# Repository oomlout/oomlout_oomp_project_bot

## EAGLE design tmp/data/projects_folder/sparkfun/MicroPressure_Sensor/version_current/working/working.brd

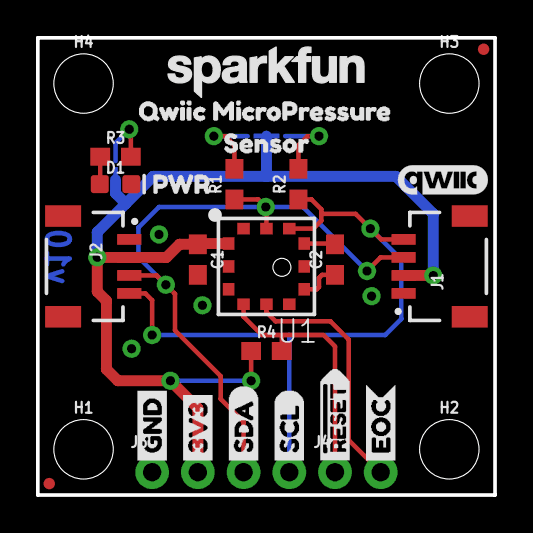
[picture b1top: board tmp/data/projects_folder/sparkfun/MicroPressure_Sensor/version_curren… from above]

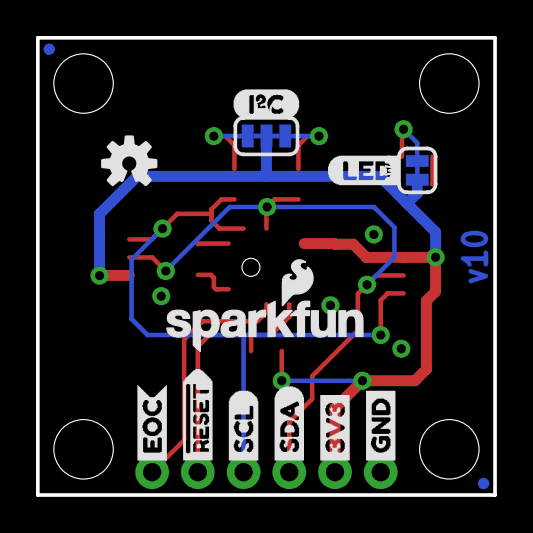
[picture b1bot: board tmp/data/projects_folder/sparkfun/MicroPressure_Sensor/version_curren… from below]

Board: 2 copper layers, 25.4 x 25.4 mm, 44 parts (14 on the bottom side), 12 nets.

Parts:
C1: 0.1uF; 0603
C2: 1nF; 0603
D1: RED; LED-0603
FD1, FD2, FD3, FD4: FIDUCIALUFIDUCIAL; FIDUCIAL-MICRO
FRAME1: FRAME-LETTER; CREATIVE_COMMONS
H1, H2, H3, H4: STAND-OFF
I2C: SMT-JUMPER_3_2-NC_TRACE_SILK
J1, J2: Qwiic; JST04_1MM_RA
J3: 1X04_NO_SILK
J4: 1X02_NO_SILK
LOGO1: QWIIC_LOGO_5MM; QWIIC_5MM
LOGO2: OSHW-LOGOS; OSHW-LOGO-S
LOGO3: SFE_LOGO_NAME_FLAME.1_INCH; SFE_LOGO_NAME_FLAME_.1
PWR: SMT-JUMPER_2_NC_TRACE_SILK
R1, R2, R4: 2.2k; 0603
R3: 1k; 0603
U1: MPR Series; MPR_SERIES_PRESSURE_I2C
U$1, U$15: GND1
U$2, U$14: 3V30
U$3, U$13: SDA2
U$4, U$12: SCL3
U$5, U$11: #RESET4
U$6, U$10: EOC5
U$7: PWR0
U$8: LED7
U$9: I#C0
U$16: QWIIC_MICROPRESSURE0
U$18: SENSOR2
U$19: SFE_LOGO_NAME_.1

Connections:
3.3V: C1.1, I2C.2, J1.2, J2.2, J3.2, PWR.1, R4.1, U1.12
!RESET: J4.1, R4.2, U1.9
EOC: J4.2, U1.8
GND: C1.2, D1.C, J1.1, J2.1, J3.1, U1.10
unnamed: PWR.2, R3.2
unnamed: D1.A, R3.1
unnamed: I2C.1, R2.2
unnamed: I2C.3, R1.2
unnamed: C2.2, U1.4
unnamed: C2.1, U1.6
SCL: J1.4, J2.4, J3.4, R2.1, U1.3
SDA: J1.3, J2.3, J3.3, R1.1, U1.2

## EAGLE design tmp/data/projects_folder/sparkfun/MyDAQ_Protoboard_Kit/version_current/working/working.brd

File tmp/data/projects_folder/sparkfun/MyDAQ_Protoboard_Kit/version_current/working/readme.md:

# MyDAQ_Protoboard_Kit by sparkfun  
This is a harvested standardized copy of a project from github.  
The original project can be found at:  
https://github.com/sparkfun/MyDAQ_Protoboard_Kit  
Please consult that link for additional, details, files, and license information.  
Note: It was auto harvested and if the original repo had more than one board file or anything out of the ordinary the files here are likely not representative.

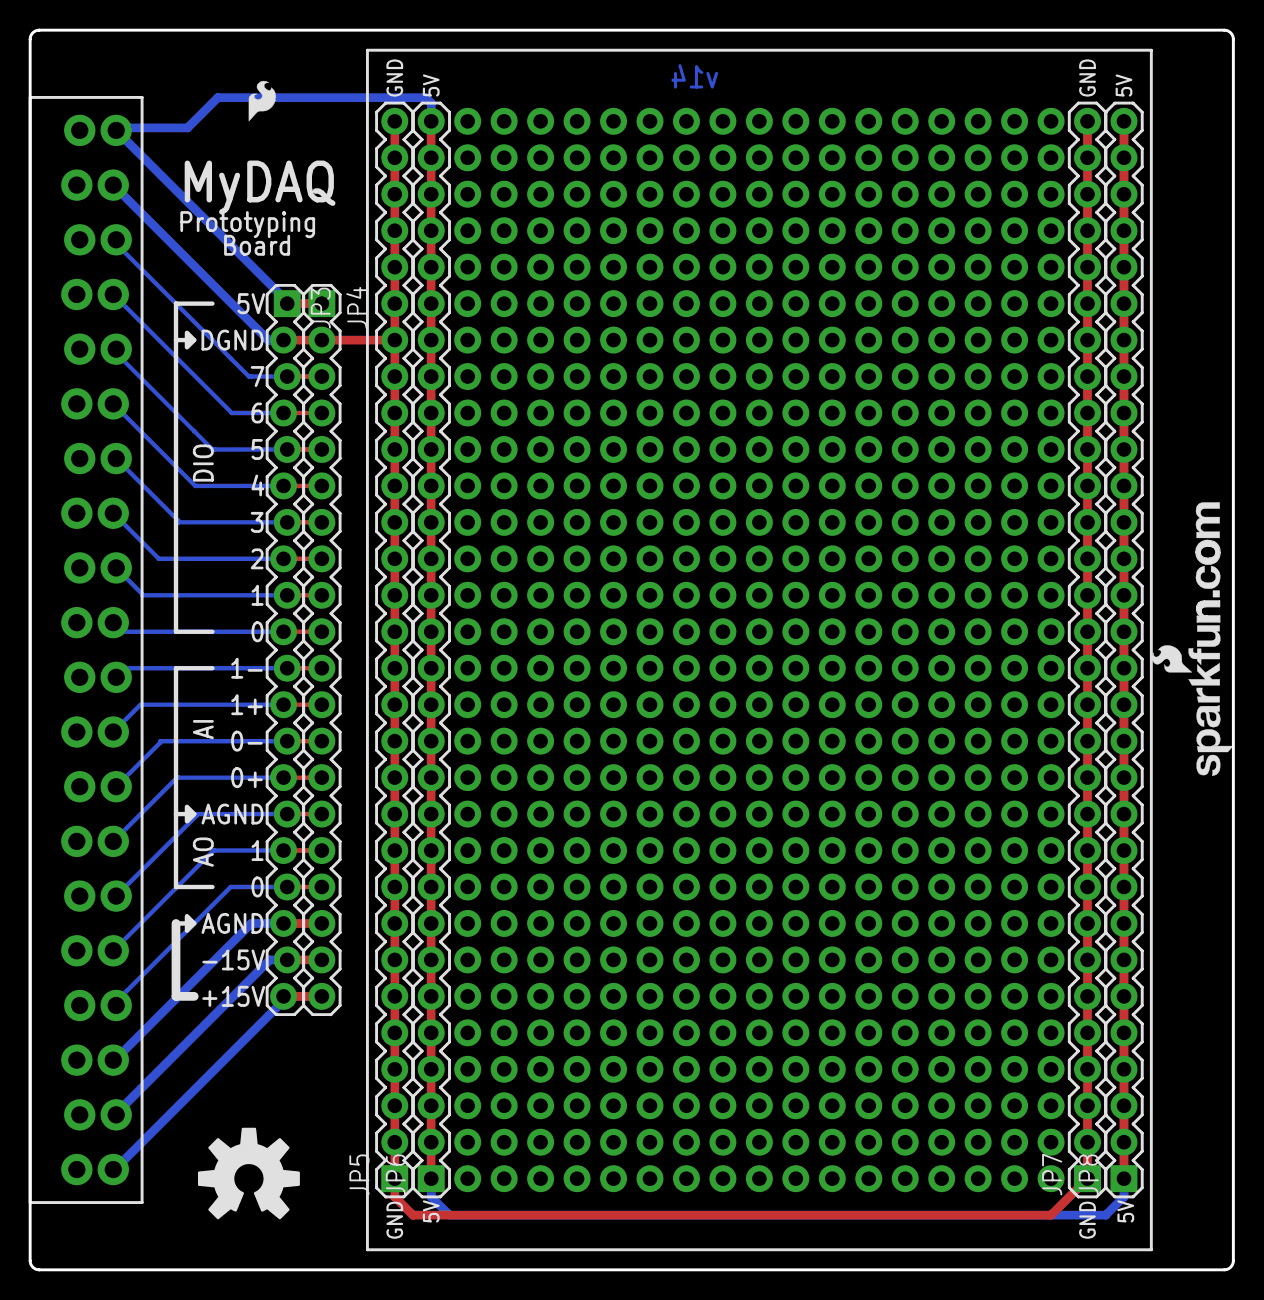
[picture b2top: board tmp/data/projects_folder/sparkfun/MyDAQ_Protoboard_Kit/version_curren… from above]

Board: 2 copper layers, 83.8 x 86.4 mm, 13 parts (0 on the bottom side), 20 nets.

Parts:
FRAME2: FRAME-LETTER; CREATIVE_COMMONS
JP1: LOGO-SFENEW; SFE-NEW-WEBLOGO
JP2: MYDAQ; 3.81MM_TERMINAL_BLOCK_FEMALE_LOCKING
JP3: M20_LOCKINGFEMALE_LOCK.009; 1X20_LOCK
JP4: M20; 1X20
JP5, JP6, JP7, JP8: M30; 1X30
LOGO1: OSHW-LOGOL; OSHW-LOGO-L
LOGO2: LOGO-SFESK; SFE-LOGO-FLAME
U1: BREADBOARDCLEAR; BREADBOARD_CLEAR
U$3: REVISION

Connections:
5V: JP2.20, JP3.1, JP4.1, JP6.1, JP6.2, JP6.3, JP6.4, JP6.5, JP6.6, JP6.7, JP6.8, JP6.9, JP6.10, JP6.11, JP6.12, JP6.13, JP6.14, JP6.15, JP6.16, JP6.17, JP6.18, JP6.19, JP6.20, JP6.21, JP6.22, JP6.23, JP6.24, JP6.25, JP6.26, JP6.27, JP6.28, JP6.29, JP6.30, JP8.1, JP8.2, JP8.3, JP8.4, JP8.5, JP8.6, JP8.7, JP8.8, JP8.9, JP8.10, JP8.11, JP8.12, JP8.13, JP8.14, JP8.15, JP8.16, JP8.17, JP8.18, JP8.19, JP8.20, JP8.21, JP8.22, JP8.23, JP8.24, JP8.25, JP8.26, JP8.27, JP8.28, JP8.29, JP8.30
+15V: JP2.1, JP3.20, JP4.20
-15V: JP2.2, JP3.19, JP4.19
AGND_15V: JP2.3, JP3.18, JP4.18
AGND_IO: JP2.6, JP3.15, JP4.15
AI0+: JP2.7, JP3.14, JP4.14
AI0-: JP2.8, JP3.13, JP4.13
AI1+: JP2.9, JP3.12, JP4.12
AI1-: JP2.10, JP3.11, JP4.11
AO0: JP2.4, JP3.17, JP4.17
AO1: JP2.5, JP3.16, JP4.16
DIO0: JP2.11, JP3.10, JP4.10
DIO1: JP2.12, JP3.9, JP4.9
DIO2: JP2.13, JP3.8, JP4.8
DIO3: JP2.14, JP3.7, JP4.7
DIO4: JP2.15, JP3.6, JP4.6
DIO5: JP2.16, JP3.5, JP4.5
DIO6: JP2.17, JP3.4, JP4.4
DIO7: JP2.18, JP3.3, JP4.3
GND: JP2.19, JP3.2, JP4.2, JP5.1, JP5.2, JP5.3, JP5.4, JP5.5, JP5.6, JP5.7, JP5.8, JP5.9, JP5.10, JP5.11, JP5.12, JP5.13, JP5.14, JP5.15, JP5.16, JP5.17, JP5.18, JP5.19, JP5.20, JP5.21, JP5.22, JP5.23, JP5.24, JP5.25, JP5.26, JP5.27, JP5.28, JP5.29, JP5.30, JP7.1, JP7.2, JP7.3, JP7.4, JP7.5, JP7.6, JP7.7, JP7.8, JP7.9, JP7.10, JP7.11, JP7.12, JP7.13, JP7.14, JP7.15, JP7.16, JP7.17, JP7.18, JP7.19, JP7.20, JP7.21, JP7.22, JP7.23, JP7.24, JP7.25, JP7.26, JP7.27, JP7.28, JP7.29, JP7.30

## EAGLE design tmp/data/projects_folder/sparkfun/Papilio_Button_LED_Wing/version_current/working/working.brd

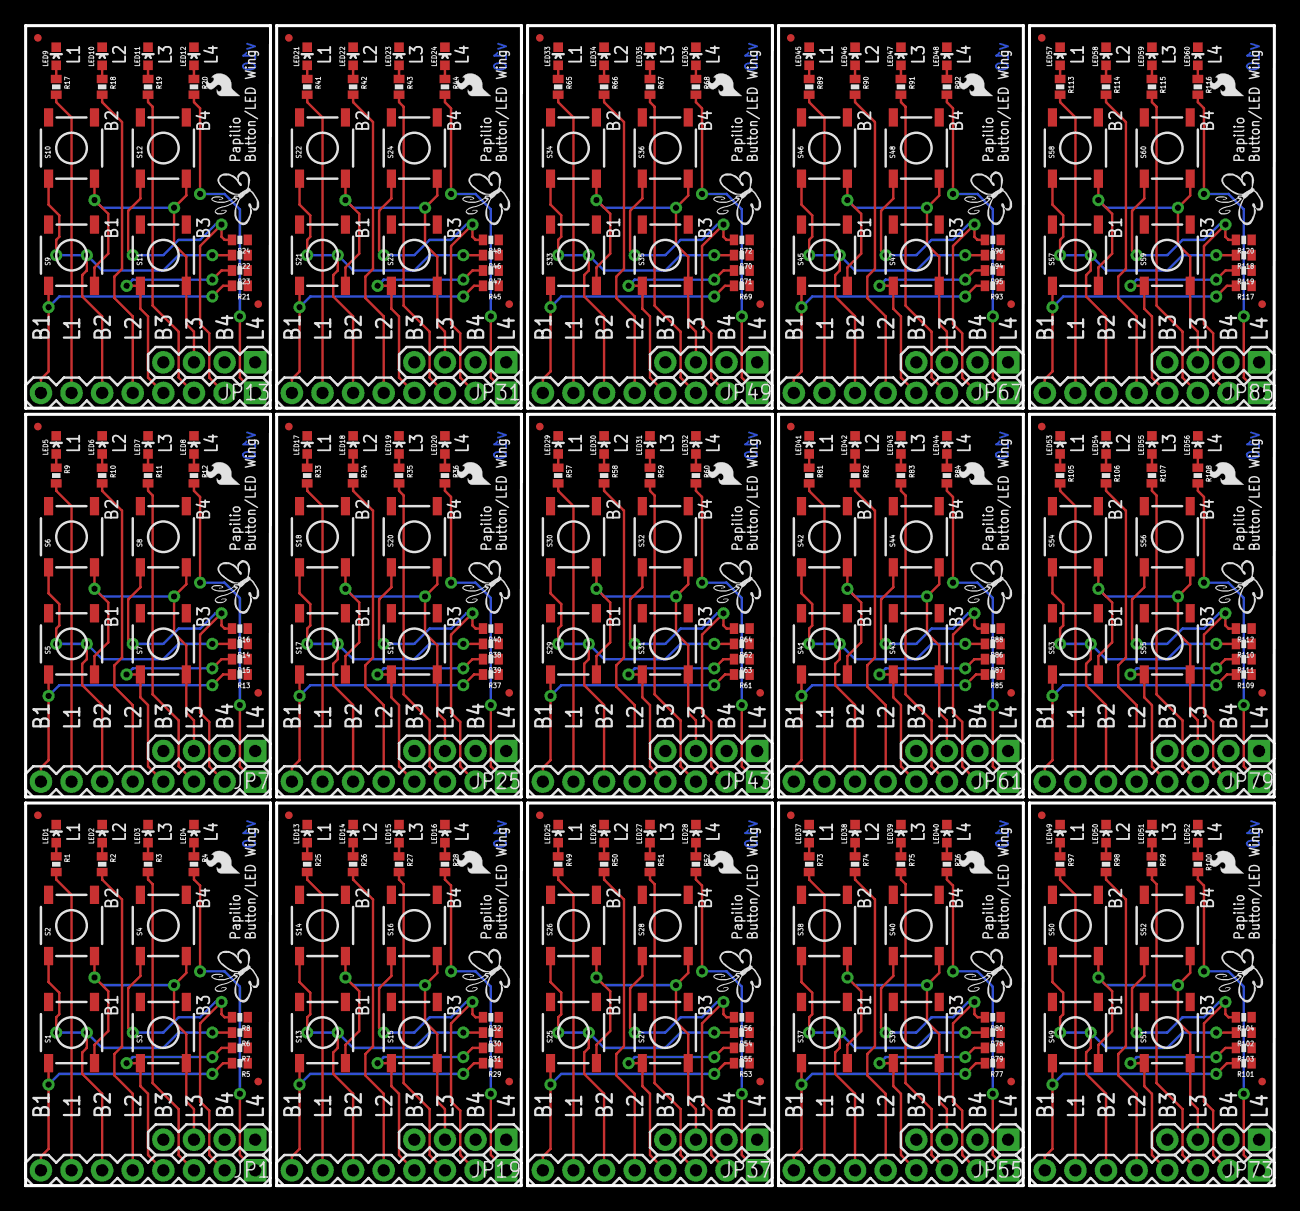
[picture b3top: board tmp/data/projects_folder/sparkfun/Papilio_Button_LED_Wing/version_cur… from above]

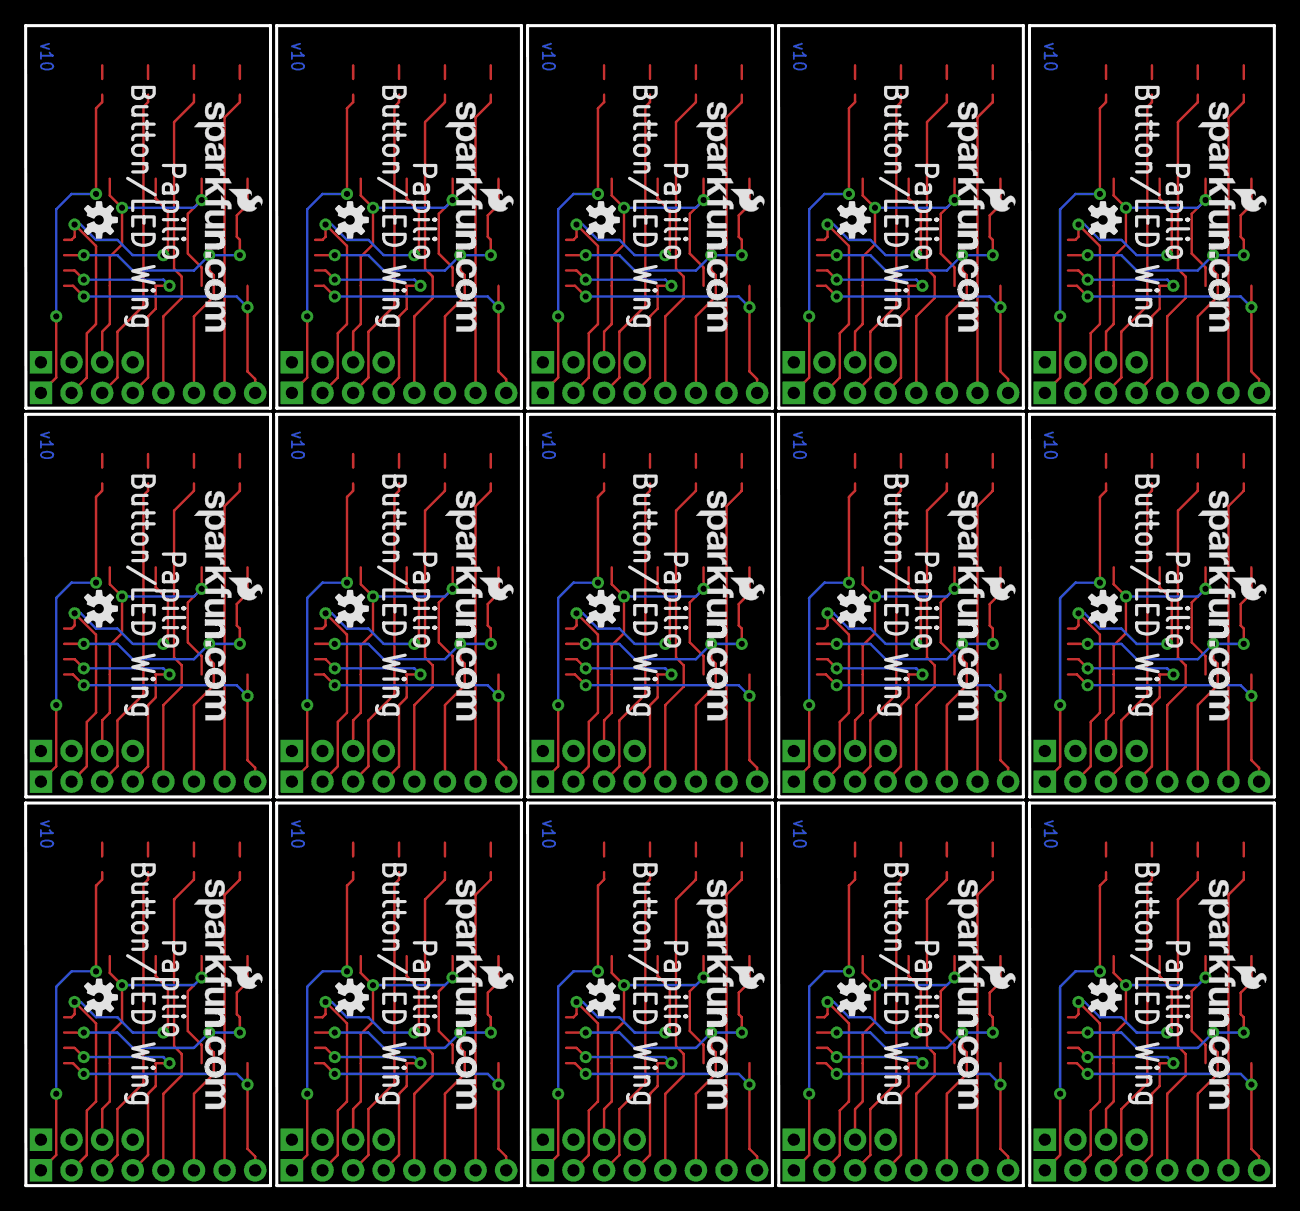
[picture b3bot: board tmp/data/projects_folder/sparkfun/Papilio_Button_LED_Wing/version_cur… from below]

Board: 2 copper layers, 103.6 x 96.3 mm, 345 parts (30 on the bottom side), 210 nets.

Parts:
JP1, JP7, JP13, JP19, JP25, JP31, JP37, JP43, JP49, JP55, JP61, JP67, JP73, JP79, JP85: 1X04
JP2, JP8, JP14, JP20, JP26, JP32, JP38, JP44, JP50, JP56, JP62, JP68, JP74, JP80, JP86: 1X08
JP3, JP9, JP15, JP21, JP27, JP33, JP39, JP45, JP51, JP57, JP63, JP69, JP75, JP81, JP87: LOGO-SFESK; SFE-LOGO-FLAME
JP4, JP10, JP16, JP22, JP28, JP34, JP40, JP46, JP52, JP58, JP64, JP70, JP76, JP82, JP88: LOGO-SFENEW; SFE-NEW-WEBLOGO
JP5, JP6, JP11, JP12, JP17, JP18, JP23, JP24, JP29, JP30, JP35, JP36, JP41, JP42, JP47, JP48, JP53, JP54, JP59, JP60, JP65, JP66, JP71, JP72, JP77, JP78, JP83, JP84, JP89, JP90: FIDUCIALUFIDUCIAL; MICRO-FIDUCIAL
LED1, LED5, LED9, LED13, LED17, LED21, LED25, LED29, LED33, LED37, LED41, LED45, LED49, LED53, LED57: Red; LED-0603
LED2, LED6, LED10, LED14, LED18, LED22, LED26, LED30, LED34, LED38, LED42, LED46, LED50, LED54, LED58: Yellow; LED-0603
LED3, LED7, LED11, LED15, LED19, LED23, LED27, LED31, LED35, LED39, LED43, LED47, LED51, LED55, LED59: Green; LED-0603
LED4, LED8, LED12, LED16, LED20, LED24, LED28, LED32, LED36, LED40, LED44, LED48, LED52, LED56, LED60: Blue; LED-0603
R1, R2, R3, R4, R9, R10, R11, R12, R17, R18, R19, R20, R25, R26, R27, R28, R33, R34, R35, R36, R41, R42, R43, R44, R49, R50, R51, R52, R57, R58, R59, R60, R65, R66, R67, R68, R73, R74, R75, R76, R81, R82, R83, R84, R89, R90, R91, R92, R97, R98, R99, R100, R105, R106, R107, R108, R113, R114, R115, R116: 220; 0402-RES
R5, R6, R7, R8, R13, R14, R15, R16, R21, R22, R23, R24, R29, R30, R31, R32, R37, R38, R39, R40, R45, R46, R47, R48, R53, R54, R55, R56, R61, R62, R63, R64, R69, R70, R71, R72, R77, R78, R79, R80, R85, R86, R87, R88, R93, R94, R95, R96, R101, R102, R103, R104, R109, R110, R111, R112, R117, R118, R119, R120: 10k; 0402-RES
S1, S5, S9, S13, S17, S21, S25, S29, S33, S37, S41, S45, S49, S53, S57: Button 1; TACTILE_SWITCH_SMD
S2, S6, S10, S14, S18, S22, S26, S30, S34, S38, S42, S46, S50, S54, S58: Button 2; TACTILE_SWITCH_SMD
S3, S7, S11, S15, S19, S23, S27, S31, S35, S39, S43, S47, S51, S55, S59: Button 3; TACTILE_SWITCH_SMD
S4, S8, S12, S16, S20, S24, S28, S32, S36, S40, S44, S48, S52, S56, S60: Button 4; TACTILE_SWITCH_SMD
U$1, U$2, U$3, U$4, U$5, U$6, U$7, U$8, U$9, U$10, U$11, U$12, U$13, U$14, U$15: OSHW-LOGOS; OSHW-LOGO-S

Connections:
3.3V: JP1.3, S1.3, S2.3, S3.3, S4.3
3.3V1: JP7.3, S5.3, S6.3, S7.3, S8.3
3.3V2: JP13.3, S9.3, S10.3, S11.3, S12.3
3.3V3: JP19.3, S13.3, S14.3, S15.3, S16.3
3.3V4: JP25.3, S17.3, S18.3, S19.3, S20.3
3.3V5: JP31.3, S21.3, S22.3, S23.3, S24.3
3.3V6: JP37.3, S25.3, S26.3, S27.3, S28.3
3.3V7: JP43.3, S29.3, S30.3, S31.3, S32.3
3.3V8: JP49.3, S33.3, S34.3, S35.3, S36.3
3.3V9: JP55.3, S37.3, S38.3, S39.3, S40.3
3.3V10: JP61.3, S41.3, S42.3, S43.3, S44.3
3.3V11: JP67.3, S45.3, S46.3, S47.3, S48.3
3.3V12: JP73.3, S49.3, S50.3, S51.3, S52.3
3.3V13: JP79.3, S53.3, S54.3, S55.3, S56.3
3.3V14: JP85.3, S57.3, S58.3, S59.3, S60.3
GND: JP1.1, LED1.C, LED2.C, LED3.C, LED4.C, R5.1, R6.1, R7.1, R8.1
GND1: JP7.1, LED5.C, LED6.C, LED7.C, LED8.C, R13.1, R14.1, R15.1, R16.1
GND2: JP13.1, LED9.C, LED10.C, LED11.C, LED12.C, R21.1, R22.1, R23.1, R24.1
GND3: JP19.1, LED13.C, LED14.C, LED15.C, LED16.C, R29.1, R30.1, R31.1, R32.1
GND4: JP25.1, LED17.C, LED18.C, LED19.C, LED20.C, R37.1, R38.1, R39.1, R40.1
GND5: JP31.1, LED21.C, LED22.C, LED23.C, LED24.C, R45.1, R46.1, R47.1, R48.1
GND6: JP37.1, LED25.C, LED26.C, LED27.C, LED28.C, R53.1, R54.1, R55.1, R56.1
GND7: JP43.1, LED29.C, LED30.C, LED31.C, LED32.C, R61.1, R62.1, R63.1, R64.1
GND8: JP49.1, LED33.C, LED34.C, LED35.C, LED36.C, R69.1, R70.1, R71.1, R72.1
GND9: JP55.1, LED37.C, LED38.C, LED39.C, LED40.C, R77.1, R78.1, R79.1, R80.1
GND10: JP61.1, LED41.C, LED42.C, LED43.C, LED44.C, R85.1, R86.1, R87.1, R88.1
GND11: JP67.1, LED45.C, LED46.C, LED47.C, LED48.C, R93.1, R94.1, R95.1, R96.1
GND12: JP73.1, LED49.C, LED50.C, LED51.C, LED52.C, R101.1, R102.1, R103.1, R104.1
GND13: JP79.1, LED53.C, LED54.C, LED55.C, LED56.C, R109.1, R110.1, R111.1, R112.1
GND14: JP85.1, LED57.C, LED58.C, LED59.C, LED60.C, R117.1, R118.1, R119.1, R120.1
LED1: JP2.7, R1.2
LED2: JP2.5, R2.2
LED3: JP2.3, R3.2
LED4: JP2.1, R4.2
LED5: JP8.7, R9.2
LED6: JP8.5, R10.2
LED7: JP8.3, R11.2
LED8: JP8.1, R12.2
LED9: JP14.7, R17.2
LED10: JP14.5, R18.2
LED11: JP14.3, R19.2
LED12: JP14.1, R20.2
LED13: JP20.7, R25.2
LED14: JP20.5, R26.2
LED15: JP20.3, R27.2
LED16: JP20.1, R28.2
LED17: JP26.7, R33.2
LED18: JP26.5, R34.2
LED19: JP26.3, R35.2
LED20: JP26.1, R36.2
LED21: JP32.7, R41.2
LED22: JP32.5, R42.2
LED23: JP32.3, R43.2
LED24: JP32.1, R44.2
LED25: JP38.7, R49.2
LED26: JP38.5, R50.2
LED27: JP38.3, R51.2
LED28: JP38.1, R52.2
LED29: JP44.7, R57.2
LED30: JP44.5, R58.2
LED31: JP44.3, R59.2
LED32: JP44.1, R60.2
LED33: JP50.7, R65.2
LED34: JP50.5, R66.2
LED35: JP50.3, R67.2
LED36: JP50.1, R68.2
LED37: JP56.7, R73.2
LED38: JP56.5, R74.2
LED39: JP56.3, R75.2
LED40: JP56.1, R76.2
LED41: JP62.7, R81.2
LED42: JP62.5, R82.2
LED43: JP62.3, R83.2
LED44: JP62.1, R84.2
LED45: JP68.7, R89.2
LED46: JP68.5, R90.2
LED47: JP68.3, R91.2
LED48: JP68.1, R92.2
LED49: JP74.7, R97.2
LED50: JP74.5, R98.2
LED51: JP74.3, R99.2
LED52: JP74.1, R100.2
LED53: JP80.7, R105.2
LED54: JP80.5, R106.2
LED55: JP80.3, R107.2
LED56: JP80.1, R108.2
LED57: JP86.7, R113.2
LED58: JP86.5, R114.2
LED59: JP86.3, R115.2
LED60: JP86.1, R116.2
unnamed: LED1.A, R1.1
unnamed: LED5.A, R9.1
unnamed: LED7.A, R11.1
unnamed: LED3.A, R3.1
unnamed: LED2.A, R2.1
unnamed: LED4.A, R4.1
unnamed: LED6.A, R10.1
unnamed: LED8.A, R12.1
unnamed: LED9.A, R17.1
unnamed: LED11.A, R19.1
unnamed: LED10.A, R18.1
unnamed: LED12.A, R20.1
unnamed: LED13.A, R25.1
unnamed: LED15.A, R27.1
unnamed: LED14.A, R26.1
unnamed: LED16.A, R28.1
unnamed: LED17.A, R33.1
unnamed: LED19.A, R35.1
unnamed: LED18.A, R34.1
unnamed: LED20.A, R36.1
unnamed: LED21.A, R41.1
unnamed: LED23.A, R43.1
unnamed: LED22.A, R42.1
unnamed: LED24.A, R44.1
unnamed: LED25.A, R49.1
unnamed: LED27.A, R51.1
unnamed: LED26.A, R50.1
unnamed: LED28.A, R52.1
unnamed: LED29.A, R57.1
unnamed: LED31.A, R59.1
unnamed: LED30.A, R58.1
unnamed: LED32.A, R60.1
unnamed: LED33.A, R65.1
unnamed: LED35.A, R67.1
unnamed: LED34.A, R66.1
unnamed: LED36.A, R68.1
unnamed: LED37.A, R73.1
unnamed: LED39.A, R75.1
unnamed: LED38.A, R74.1
unnamed: LED40.A, R76.1
unnamed: LED41.A, R81.1
unnamed: LED43.A, R83.1
unnamed: LED42.A, R82.1
unnamed: LED44.A, R84.1
unnamed: LED45.A, R89.1
unnamed: LED47.A, R91.1
unnamed: LED46.A, R90.1
unnamed: LED48.A, R92.1
unnamed: LED49.A, R97.1
unnamed: LED51.A, R99.1
unnamed: LED50.A, R98.1
unnamed: LED52.A, R100.1
unnamed: LED53.A, R105.1
unnamed: LED55.A, R107.1
unnamed: LED54.A, R106.1
unnamed: LED56.A, R108.1
unnamed: LED57.A, R113.1
unnamed: LED59.A, R115.1
unnamed: LED58.A, R114.1
unnamed: LED60.A, R116.1
PB1: JP2.8, R5.2, S1.1
PB2: JP2.6, R6.2, S2.1
PB3: JP2.4, R7.2, S3.1
PB4: JP2.2, R8.2, S4.1
PB5: JP8.8, R13.2, S5.1
PB6: JP8.6, R14.2, S6.1
PB7: JP8.4, R15.2, S7.1
PB8: JP8.2, R16.2, S8.1
PB9: JP14.8, R21.2, S9.1
PB10: JP14.6, R22.2, S10.1
PB11: JP14.4, R23.2, S11.1
PB12: JP14.2, R24.2, S12.1
PB13: JP20.8, R29.2, S13.1
PB14: JP20.6, R30.2, S14.1
PB15: JP20.4, R31.2, S15.1
PB16: JP20.2, R32.2, S16.1
PB17: JP26.8, R37.2, S17.1
PB18: JP26.6, R38.2, S18.1
PB19: JP26.4, R39.2, S19.1
PB20: JP26.2, R40.2, S20.1
PB21: JP32.8, R45.2, S21.1
PB22: JP32.6, R46.2, S22.1
PB23: JP32.4, R47.2, S23.1
PB24: JP32.2, R48.2, S24.1
PB25: JP38.8, R53.2, S25.1
PB26: JP38.6, R54.2, S26.1
PB27: JP38.4, R55.2, S27.1
PB28: JP38.2, R56.2, S28.1
PB29: JP44.8, R61.2, S29.1
PB30: JP44.6, R62.2, S30.1
PB31: JP44.4, R63.2, S31.1
PB32: JP44.2, R64.2, S32.1
PB33: JP50.8, R69.2, S33.1
PB34: JP50.6, R70.2, S34.1
PB35: JP50.4, R71.2, S35.1
PB36: JP50.2, R72.2, S36.1
PB37: JP56.8, R77.2, S37.1
PB38: JP56.6, R78.2, S38.1
PB39: JP56.4, R79.2, S39.1
PB40: JP56.2, R80.2, S40.1
PB41: JP62.8, R85.2, S41.1
PB42: JP62.6, R86.2, S42.1
PB43: JP62.4, R87.2, S43.1
PB44: JP62.2, R88.2, S44.1
PB45: JP68.8, R93.2, S45.1
PB46: JP68.6, R94.2, S46.1
PB47: JP68.4, R95.2, S47.1
PB48: JP68.2, R96.2, S48.1
PB49: JP74.8, R101.2, S49.1
PB50: JP74.6, R102.2, S50.1
PB51: JP74.4, R103.2, S51.1
PB52: JP74.2, R104.2, S52.1
PB53: JP80.8, R109.2, S53.1
PB54: JP80.6, R110.2, S54.1
PB55: JP80.4, R111.2, S55.1
PB56: JP80.2, R112.2, S56.1
PB57: JP86.8, R117.2, S57.1
PB58: JP86.6, R118.2, S58.1
PB59: JP86.4, R119.2, S59.1
PB60: JP86.2, R120.2, S60.1

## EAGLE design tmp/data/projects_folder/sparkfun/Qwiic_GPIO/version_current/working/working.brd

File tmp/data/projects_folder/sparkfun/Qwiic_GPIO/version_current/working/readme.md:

# Qwiic_GPIO by sparkfun  
This is a harvested standardized copy of a project from github.  
The original project can be found at:  
https://github.com/sparkfun/Qwiic_GPIO  
Please consult that link for additional, details, files, and license information.  
Note: It was auto harvested and if the original repo had more than one board file or anything out of the ordinary the files here are likely not representative.

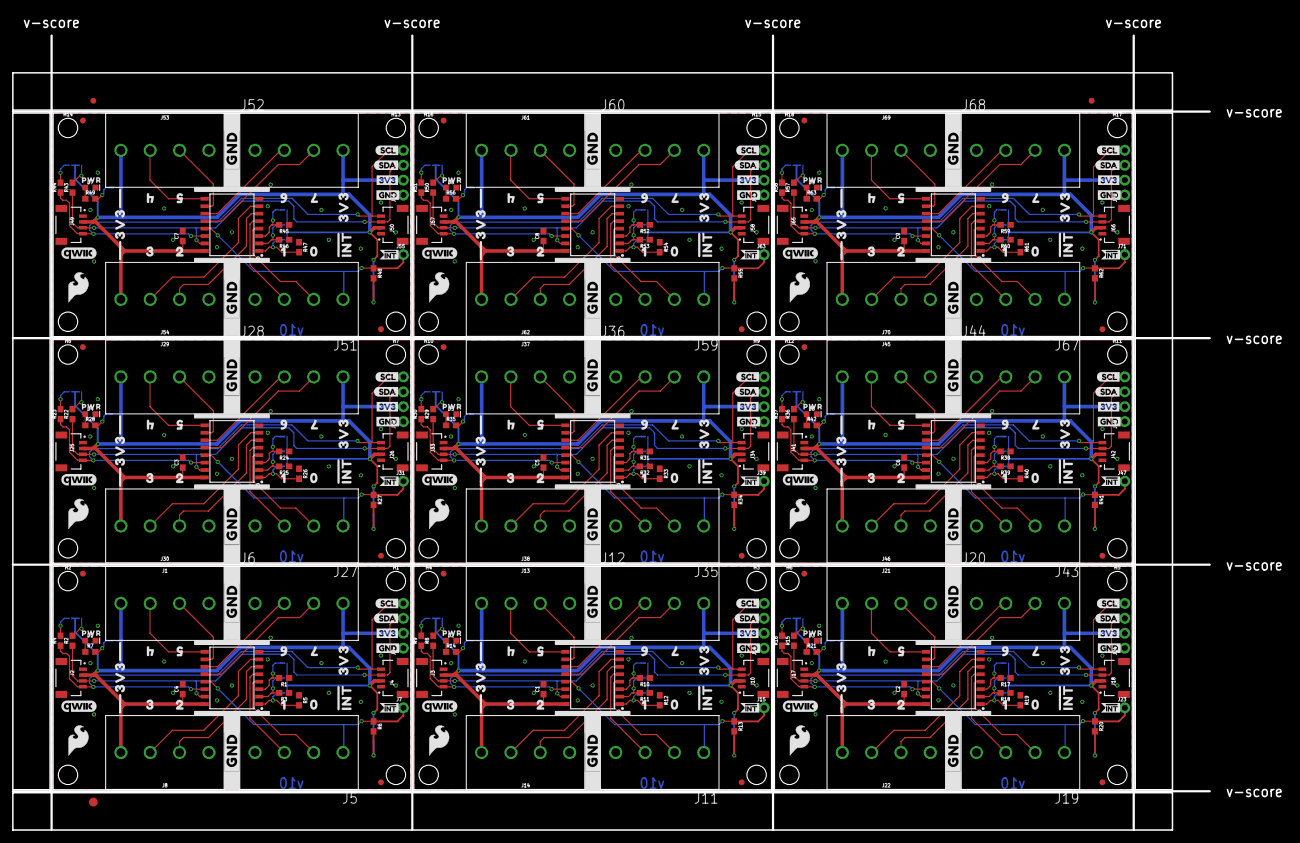
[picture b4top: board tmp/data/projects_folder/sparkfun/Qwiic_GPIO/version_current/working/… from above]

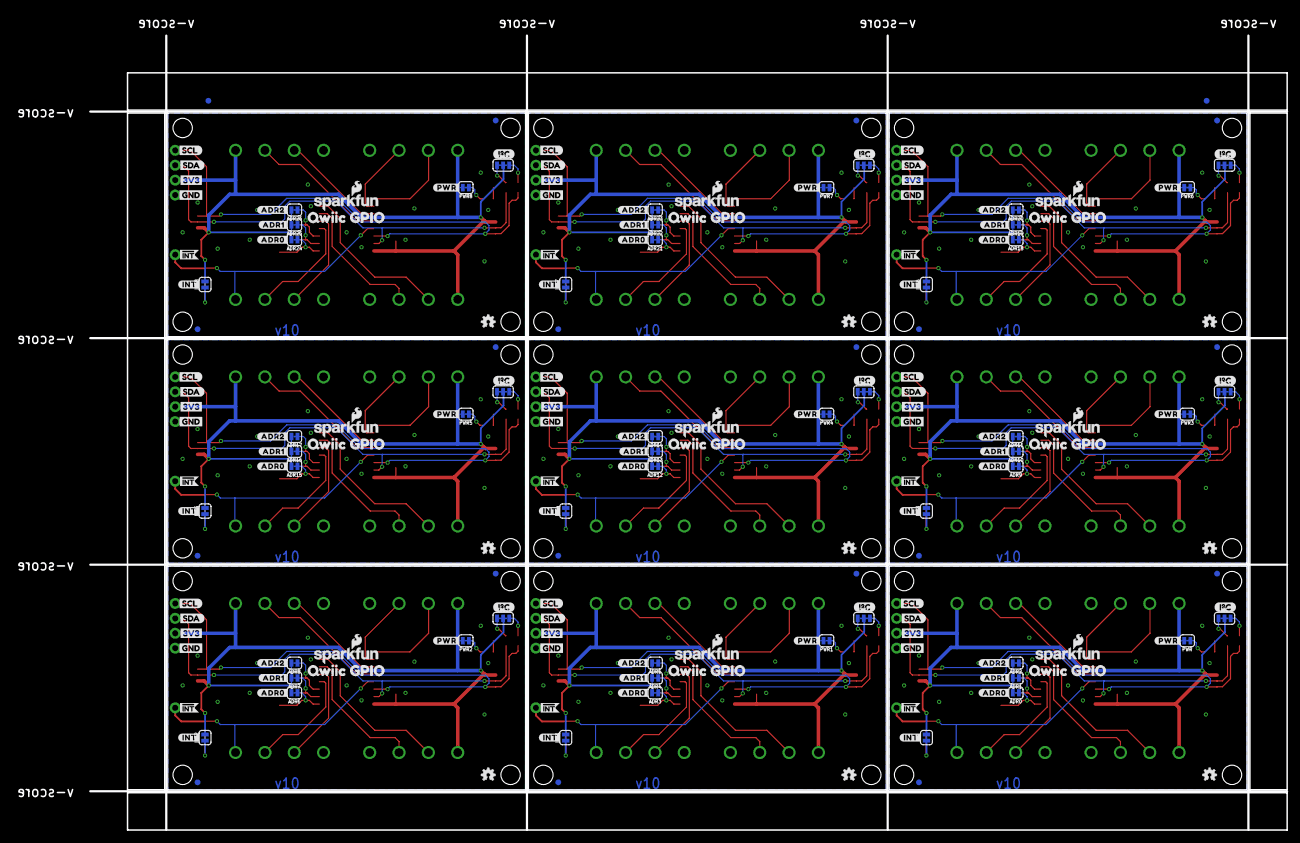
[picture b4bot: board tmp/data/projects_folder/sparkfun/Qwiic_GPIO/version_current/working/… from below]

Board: 2 copper layers, 204.0 x 135.4 mm, 626 parts (200 on the bottom side), 189 nets.

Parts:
ADR0, ADR1, ADR2, ADR3, ADR4, ADR5, ADR6, ADR7, ADR8, ADR9, ADR10, ADR11, ADR12, ADR13, ADR14, ADR15, ADR16, ADR17, ADR18, ADR19, ADR20, ADR21, ADR22, ADR23, ADR24, ADR25, ADR26: JUMPER-SMT_2_NC_TRACE_SILK; SMT-JUMPER_2_NC_TRACE_SILK
C1, C2, C3, C4, C5, C6, C7, C8, C9: 0.1uF; 0603
D1, D2, D3, D4, D5, D6, D7, D8, D9: RED; LED-0603
E$1, E$2, E$3, E$4: FIDUCIAL-1X2
E$5: FIDUCIAL-1.5X3
FD1, FD2, FD3, FD4, FD5, FD6, FD7, FD8, FD9, FD10, FD11, FD12, FD13, FD14, FD15, FD16, FD17, FD18: FIDUCIAL1X2; FIDUCIAL-1X2
FRAME1, FRAME2, FRAME3, FRAME4, FRAME5, FRAME6, FRAME7, FRAME8, FRAME9: FRAME-LETTER; CREATIVE_COMMONS
H1, H2, H3, H4, H5, H6, H7, H8, H9, H10, H11, H12, H13, H14, H15, H16, H17, H18: STAND-OFF
I2C, I2C1, I2C2, I2C3, I2C4, I2C5, I2C6, I2C7, I2C8: JUMPER-SMT_3_2-NC_TRACE_SILK; SMT-JUMPER_3_2-NC_TRACE_SILK
INT, INT1, INT2, INT3, INT4, INT5, INT6, INT7, INT8: JUMPER-SMT_2_NC_TRACE_SILK; SMT-JUMPER_2_NC_TRACE_SILK
J1, J5, J6, J8, J11, J12, J13, J14, J19, J20, J21, J22, J27, J28, J29, J30, J35, J36, J37, J38, J43, J44, J45, J46, J51, J52, J53, J54, J59, J60, J61, J62, J67, J68, J69, J70: LATCHTERMINAL-5MM-4
J2, J3, J4, J10, J17, J18, J25, J26, J33, J34, J41, J42, J49, J50, J57, J58, J65, J66: QWIIC; JST04_1MM_RA
J7, J15, J23, J31, J39, J47, J55, J63, J71: 1X01_NO_SILK
J9, J16, J24, J32, J40, J48, J56, J64, J72: 1X04_NO_SILK
JP1, JP3, JP4, JP5, JP9, JP10, JP13, JP14, JP17, JP18, JP21, JP22, JP25, JP26, JP29, JP30, JP33, JP34: STAND-OFF
JP2, JP6, JP7, JP8, JP11, JP12, JP15, JP16, JP19, JP20, JP23, JP24, JP27, JP28, JP31, JP32, JP35, JP36: FIDUCIAL1X2; FIDUCIAL-1X2
LOGO1, LOGO5, LOGO9, LOGO13, LOGO17, LOGO21, LOGO25, LOGO29, LOGO33: OSHW-LOGOMINI; OSHW-LOGO-MINI
LOGO2, LOGO6, LOGO10, LOGO14, LOGO18, LOGO22, LOGO26, LOGO30, LOGO34: REVISION
LOGO3, LOGO7, LOGO11, LOGO15, LOGO19, LOGO23, LOGO27, LOGO31, LOGO35: SFE_LOGO_NAME_FLAME.1_INCH; SFE_LOGO_NAME_FLAME_.1
LOGO4, LOGO8, LOGO12, LOGO16, LOGO20, LOGO24, LOGO28, LOGO32, LOGO36: SFE_LOGO_FLAME.2_INCH; SFE_LOGO_FLAME_.2
PWR, PWR1, PWR2, PWR3, PWR4, PWR5, PWR6, PWR7, PWR8: JUMPER-SMT_2_NC_TRACE_SILK; SMT-JUMPER_2_NC_TRACE_SILK
R1, R2, R3, R4, R5, R8, R9, R10, R11, R12, R15, R16, R17, R18, R19, R22, R23, R24, R25, R26, R29, R30, R31, R32, R33, R36, R37, R38, R39, R40, R43, R44, R45, R46, R47, R50, R51, R52, R53, R54, R57, R58, R59, R60, R61: 2.2k; 0603
R6, R13, R20, R27, R34, R41, R48, R55, R62: 10k; 0603
R7, R14, R21, R28, R35, R42, R49, R56, R63: 1k; 0603
U1, U2, U3, U4, U5, U6, U7, U8, U9: TCA9534; 16SOIC
U$1, U$45, U$77, U$109, U$141, U$173, U$205, U$237, U$269: I2C
U$2, U$49, U$81, U$113, U$145, U$177, U$209, U$241, U$273: 20
U$3, U$16, U$26, U$42, U$65, U$74, U$97, U$106, U$129, U$138, U$161, U$170, U$193, U$202, U$225, U$234, U$257, U$266: 3V33
U$4, U$50, U$82, U$114, U$146, U$178, U$210, U$242, U$274: 30
U$5, U$63, U$95, U$127, U$159, U$191, U$223, U$255, U$287: #ADR1#0
U$6, U$51, U$83, U$115, U$147, U$179, U$211, U$243, U$275: 10
U$7, U$17, U$25, U$41, U$66, U$73, U$98, U$105, U$130, U$137, U$162, U$169, U$194, U$201, U$226, U$233, U$258, U$265: GND4
U$8, U$18, U$67, U$99, U$131, U$163, U$195, U$227, U$259: QWIIC_GPIO7
U$9, U$19, U$68, U$100, U$132, U$164, U$196, U$228, U$260: SCL6
U$10, U$20, U$69, U$101, U$133, U$165, U$197, U$229, U$261: SDA5
U$11, U$64, U$96, U$128, U$160, U$192, U$224, U$256, U$288: #ADR2#0
U$12, U$47, U$79, U$111, U$143, U$175, U$207, U$239, U$271: #INT#0
U$13, U$22, U$29, U$43, U$44, U$53, U$75, U$76, U$85, U$107, U$108, U$117, U$139, U$140, U$149, U$171, U$172, U$181, U$203, U$204, U$213, U$235, U$236, U$245, U$267, U$268, U$277: #INT0
U$14, U$52, U$84, U$116, U$148, U$180, U$212, U$244, U$276: 00
U$15, U$62, U$94, U$126, U$158, U$190, U$222, U$254, U$286: #ADR0#0
U$21, U$27, U$70, U$102, U$134, U$166, U$198, U$230, U$262: QWIIC_6MM
U$23, U$28, U$71, U$103, U$135, U$167, U$199, U$231, U$263: SCL0
U$24, U$36, U$72, U$104, U$136, U$168, U$200, U$232, U$264: SDA1
U$30, U$31, U$54, U$55, U$86, U$87, U$118, U$119, U$150, U$151, U$182, U$183, U$214, U$215, U$246, U$247, U$278, U$279: 3V30
U$32, U$56, U$88, U$120, U$152, U$184, U$216, U$248, U$280: 40
U$33, U$57, U$89, U$121, U$153, U$185, U$217, U$249, U$281: 50
U$34, U$46, U$78, U$110, U$142, U$174, U$206, U$238, U$270: PWR0
U$35, U$58, U$90, U$122, U$154, U$186, U$218, U$250, U$282: 60
U$37, U$59, U$91, U$123, U$155, U$187, U$219, U$251, U$283: 70
U$38, U$40, U$60, U$61, U$92, U$93, U$124, U$125, U$156, U$157, U$188, U$189, U$220, U$221, U$252, U$253, U$284, U$285: #GND#0
U$39, U$48, U$80, U$112, U$144, U$176, U$208, U$240, U$272: #PWR#0

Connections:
3.3V: ADR0.2, ADR1.2, ADR2.2, C4.1, I2C.2, INT.2, J1.1, J2.2, J4.2, J6.4, J8.4, J9.2, PWR.2, U3.16
3.3V1: ADR3.2, ADR4.2, ADR5.2, C1.1, I2C1.2, INT1.2, J3.2, J10.2, J12.4, J13.1, J14.4, J16.2, PWR1.2, U1.16
3.3V2: ADR6.2, ADR7.2, ADR8.2, C2.1, I2C2.2, INT2.2, J17.2, J18.2, J20.4, J21.1, J22.4, J24.2, PWR2.2, U2.16
3.3V3: ADR9.2, ADR10.2, ADR11.2, C3.1, I2C3.2, INT3.2, J25.2, J26.2, J28.4, J29.1, J30.4, J32.2, PWR3.2, U4.16
3.3V4: ADR12.2, ADR13.2, ADR14.2, C5.1, I2C4.2, INT4.2, J33.2, J34.2, J36.4, J37.1, J38.4, J40.2, PWR4.2, U5.16
3.3V5: ADR15.2, ADR16.2, ADR17.2, C6.1, I2C5.2, INT5.2, J41.2, J42.2, J44.4, J45.1, J46.4, J48.2, PWR5.2, U6.16
3.3V6: ADR18.2, ADR19.2, ADR20.2, C7.1, I2C6.2, INT6.2, J49.2, J50.2, J52.4, J53.1, J54.4, J56.2, PWR6.2, U7.16
3.3V7: ADR21.2, ADR22.2, ADR23.2, C8.1, I2C7.2, INT7.2, J57.2, J58.2, J60.4, J61.1, J62.4, J64.2, PWR7.2, U8.16
3.3V8: ADR24.2, ADR25.2, ADR26.2, C9.1, I2C8.2, INT8.2, J65.2, J66.2, J68.4, J69.1, J70.4, J72.2, PWR8.2, U9.16
!INT: J5.1, J7.1, R6.1, U3.13
!INT1: J11.1, J15.1, R13.1, U1.13
!INT2: J19.1, J23.1, R20.1, U2.13
!INT3: J27.1, J31.1, R27.1, U4.13
!INT4: J35.1, J39.1, R34.1, U5.13
!INT5: J43.1, J47.1, R41.1, U6.13
!INT6: J51.1, J55.1, R48.1, U7.13
!INT7: J59.1, J63.1, R55.1, U8.13
!INT8: J67.1, J71.1, R62.1, U9.13
ADR0: ADR0.1, R5.2, U3.1
ADR1: ADR1.1, R3.2, U3.2
ADR2: ADR2.1, R1.2, U3.3
ADR3: ADR3.1, R12.2, U1.1
ADR4: ADR4.1, R11.2, U1.2
ADR5: ADR5.1, R10.2, U1.3
ADR6: ADR6.1, R19.2, U2.1
ADR7: ADR7.1, R18.2, U2.2
ADR8: ADR8.1, R17.2, U2.3
ADR9: ADR9.1, R26.2, U4.1
ADR10: ADR10.1, R25.2, U4.2
ADR11: ADR11.1, R24.2, U4.3
ADR12: ADR12.1, R33.2, U5.1
ADR13: ADR13.1, R32.2, U5.2
ADR14: ADR14.1, R31.2, U5.3
ADR15: ADR15.1, R40.2, U6.1
ADR16: ADR16.1, R39.2, U6.2
ADR17: ADR17.1, R38.2, U6.3
ADR18: ADR18.1, R47.2, U7.1
ADR19: ADR19.1, R46.2, U7.2
ADR20: ADR20.1, R45.2, U7.3
ADR21: ADR21.1, R54.2, U8.1
ADR22: ADR22.1, R53.2, U8.2
ADR23: ADR23.1, R52.2, U8.3
ADR24: ADR24.1, R61.2, U9.1
ADR25: ADR25.1, R60.2, U9.2
ADR26: ADR26.1, R59.2, U9.3
GND: C4.2, D1.C, J1.4, J2.1, J4.1, J5.4, J6.1, J8.1, J9.1, R1.1, R3.1, R5.1, U3.8
GND1: C1.2, D2.C, J3.1, J10.1, J11.4, J12.1, J13.4, J14.1, J16.1, R10.1, R11.1, R12.1, U1.8
GND2: C2.2, D3.C, J17.1, J18.1, J19.4, J20.1, J21.4, J22.1, J24.1, R17.1, R18.1, R19.1, U2.8
GND3: C3.2, D4.C, J25.1, J26.1, J27.4, J28.1, J29.4, J30.1, J32.1, R24.1, R25.1, R26.1, U4.8
GND4: C5.2, D5.C, J33.1, J34.1, J35.4, J36.1, J37.4, J38.1, J40.1, R31.1, R32.1, R33.1, U5.8
GND5: C6.2, D6.C, J41.1, J42.1, J43.4, J44.1, J45.4, J46.1, J48.1, R38.1, R39.1, R40.1, U6.8
GND6: C7.2, D7.C, J49.1, J50.1, J51.4, J52.1, J53.4, J54.1, J56.1, R45.1, R46.1, R47.1, U7.8
GND7: C8.2, D8.C, J57.1, J58.1, J59.4, J60.1, J61.4, J62.1, J64.1, R52.1, R53.1, R54.1, U8.8
GND8: C9.2, D9.C, J65.1, J66.1, J67.4, J68.1, J69.4, J70.1, J72.1, R59.1, R60.1, R61.1, U9.8
unnamed: INT.1, R6.2
unnamed: D1.A, R7.1
unnamed: PWR.1, R7.2
unnamed: INT1.1, R13.2
unnamed: D2.A, R14.1
unnamed: PWR1.1, R14.2
unnamed: INT2.1, R20.2
unnamed: D3.A, R21.1
unnamed: PWR2.1, R21.2
unnamed: INT3.1, R27.2
unnamed: D4.A, R28.1
unnamed: PWR3.1, R28.2
unnamed: INT4.1, R34.2
unnamed: D5.A, R35.1
unnamed: PWR4.1, R35.2
unnamed: INT5.1, R41.2
unnamed: D6.A, R42.1
unnamed: PWR5.1, R42.2
unnamed: INT6.1, R48.2
unnamed: D7.A, R49.1
unnamed: PWR6.1, R49.2
unnamed: INT7.1, R55.2
unnamed: D8.A, R56.1
unnamed: PWR7.1, R56.2
unnamed: INT8.1, R62.2
unnamed: D9.A, R63.1
unnamed: PWR8.1, R63.2
P0: J5.2, U3.4
P1: J5.3, U3.5
P2: J8.2, U3.6
P3: J8.3, U3.7
P4: J1.2, U3.9
P5: J1.3, U3.10
P6: J6.2, U3.11
P7: J6.3, U3.12
P8: J11.2, U1.4
P9: J14.2, U1.6
P10: J14.3, U1.7
P11: J11.3, U1.5
P12: J13.2, U1.9
P13: J13.3, U1.10
P14: J12.2, U1.11
P15: J12.3, U1.12
P16: J19.2, U2.4
P17: J22.2, U2.6
P18: J22.3, U2.7
P19: J19.3, U2.5
P20: J21.2, U2.9
P21: J21.3, U2.10
P22: J20.2, U2.11
P23: J20.3, U2.12
P24: J27.2, U4.4
P25: J30.2, U4.6
P26: J30.3, U4.7
P27: J27.3, U4.5
P28: J29.2, U4.9
P29: J29.3, U4.10
P30: J28.2, U4.11
P31: J28.3, U4.12
P32: J35.2, U5.4
P33: J38.2, U5.6
P34: J38.3, U5.7
P35: J35.3, U5.5
P36: J37.2, U5.9
P37: J37.3, U5.10
P38: J36.2, U5.11
P39: J36.3, U5.12
P40: J43.2, U6.4
P41: J46.2, U6.6
P42: J46.3, U6.7
P43: J43.3, U6.5
P44: J45.2, U6.9
P45: J45.3, U6.10
P46: J44.2, U6.11
P47: J44.3, U6.12
P48: J51.2, U7.4
P49: J54.2, U7.6
P50: J54.3, U7.7
P51: J51.3, U7.5
P52: J53.2, U7.9
P53: J53.3, U7.10
P54: J52.2, U7.11
P55: J52.3, U7.12
P56: J59.2, U8.4
P57: J62.2, U8.6
P58: J62.3, U8.7
P59: J59.3, U8.5
P60: J61.2, U8.9
P61: J61.3, U8.10
P62: J60.2, U8.11
P63: J60.3, U8.12
P64: J67.2, U9.4
P65: J70.2, U9.6
P66: J70.3, U9.7
P67: J67.3, U9.5
P68: J69.2, U9.9
P69: J69.3, U9.10
P70: J68.2, U9.11
P71: J68.3, U9.12
SCL: J2.4, J4.4, J9.4, R4.1, U3.14
SCL1: J3.4, J10.4, J16.4, R9.1, U1.14
SCL2: J17.4, J18.4, J24.4, R16.1, U2.14
SCL3: J25.4, J26.4, J32.4, R23.1, U4.14
SCL4: J33.4, J34.4, J40.4, R30.1, U5.14
SCL5: J41.4, J42.4, J48.4, R37.1, U6.14
SCL6: J49.4, J50.4, J56.4, R44.1, U7.14
SCL7: J57.4, J58.4, J64.4, R51.1, U8.14
SCL8: J65.4, J66.4, J72.4, R58.1, U9.14
SCL_PU1: I2C.1, R2.2
SCL_PU2: I2C1.1, R8.2
SCL_PU3: I2C2.1, R15.2
SCL_PU4: I2C3.1, R22.2
SCL_PU5: I2C4.1, R29.2
SCL_PU6: I2C5.1, R36.2
SCL_PU7: I2C6.1, R43.2
SCL_PU8: I2C7.1, R50.2
SCL_PU9: I2C8.1, R57.2
SDA: J2.3, J4.3, J9.3, R2.1, U3.15
SDA1: J3.3, J10.3, J16.3, R8.1, U1.15
SDA2: J17.3, J18.3, J24.3, R15.1, U2.15
SDA3: J25.3, J26.3, J32.3, R22.1, U4.15
SDA4: J33.3, J34.3, J40.3, R29.1, U5.15
SDA5: J41.3, J42.3, J48.3, R36.1, U6.15
SDA6: J49.3, J50.3, J56.3, R43.1, U7.15
SDA7: J57.3, J58.3, J64.3, R50.1, U8.15
SDA8: J65.3, J66.3, J72.3, R57.1, U9.15
SDA_PU1: I2C.3, R4.2
SDA_PU2: I2C1.3, R9.2
SDA_PU3: I2C2.3, R16.2
SDA_PU4: I2C3.3, R23.2
SDA_PU5: I2C4.3, R30.2
SDA_PU6: I2C5.3, R37.2
SDA_PU7: I2C6.3, R44.2
SDA_PU8: I2C7.3, R51.2
SDA_PU9: I2C8.3, R58.2

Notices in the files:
parts and their libraries:
SparkFun-Capacitors: Licensing: Creative Commons ShareAlike 4.0 International - https://creativecommons.org/licenses/by-sa/4.0
SparkFun-Aesthetics: Released under the Creative Commons Attribution Share-Alike 4.0 License
SparkFun-Aesthetics: https://creativecommons.org/licenses/by-sa/4.0
